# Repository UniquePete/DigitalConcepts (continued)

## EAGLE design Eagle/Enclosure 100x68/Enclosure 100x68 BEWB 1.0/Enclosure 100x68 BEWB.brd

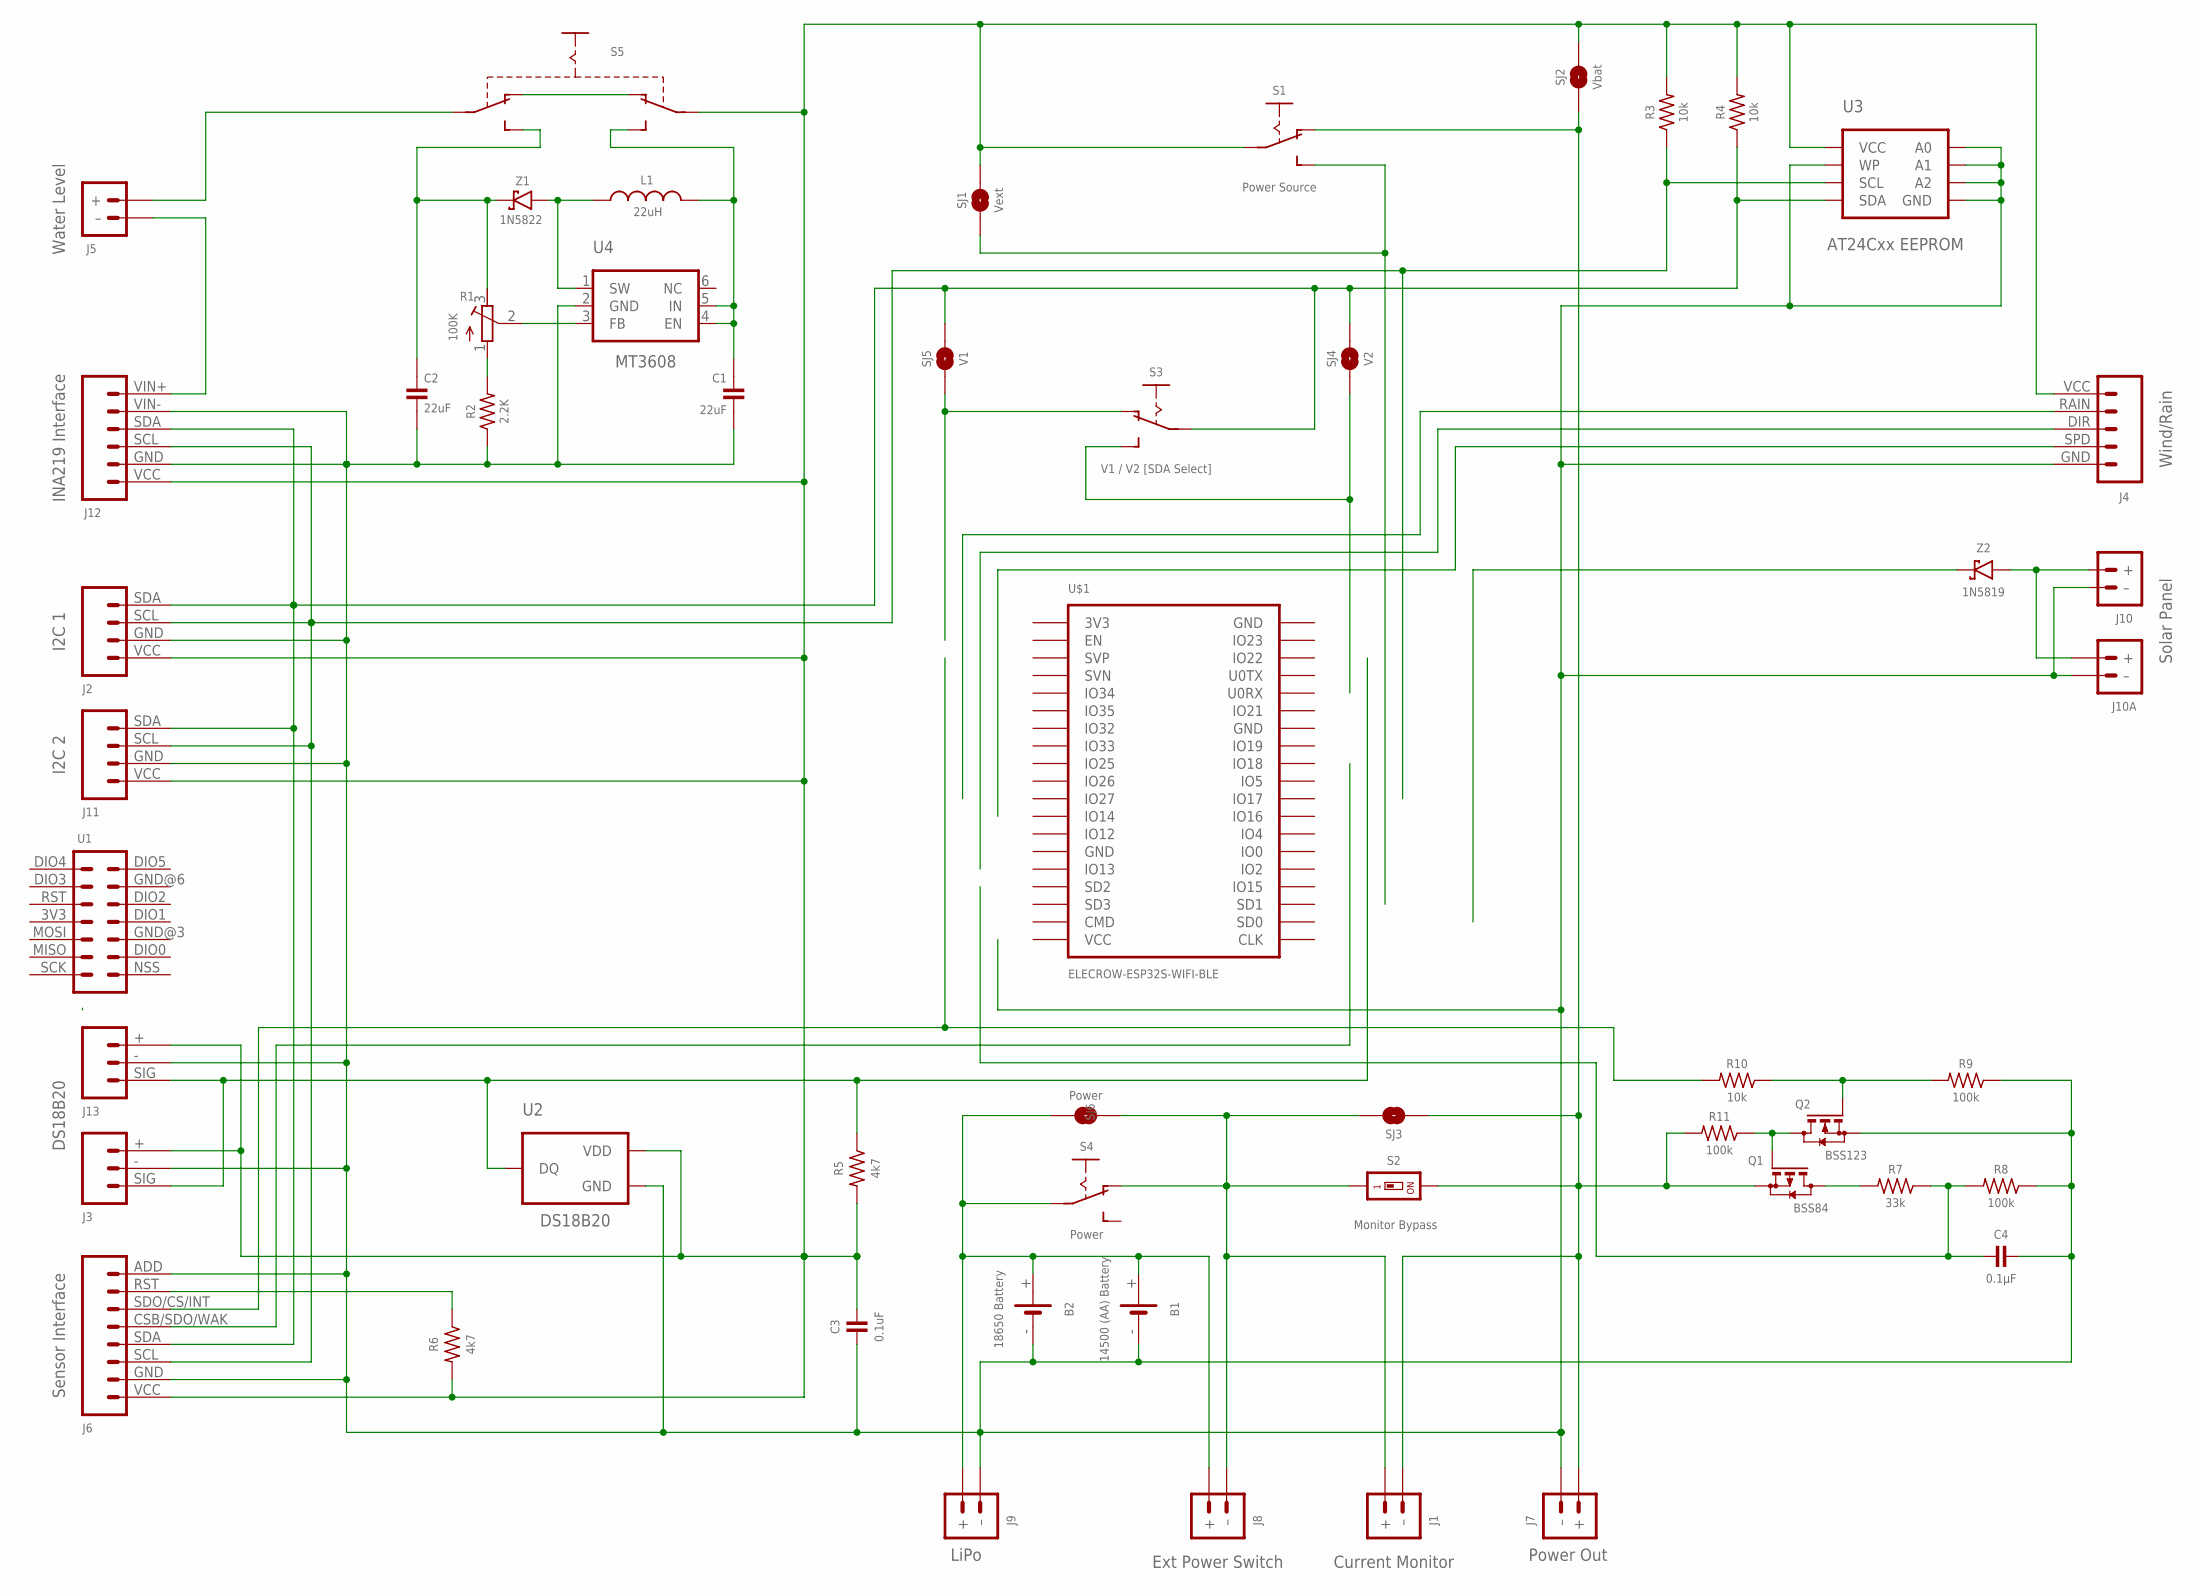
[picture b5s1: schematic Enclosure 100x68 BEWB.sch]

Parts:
B1: 14500 (AA) Battery; BATTERY-14500
B2: 18650 Battery; BATTERY-18650
C1, C2: 22uF; C1206
C3: 0.1uF; C0805
C4: 0.1µF; C0805
J1: Current Monitor; JST-PH2.0-2-HORIZONTAL
J2: I2C 1; JST-PH2.0-4-VERTICAL-I2C
J3: DS18B20; JST-PH2.0-3-VERTICAL-SIG
J4: Wind/Rain; JST-PH2.0-5-DUAL-WEATHER
J5: Water Level; JST-PH2.0-2-DUAL-POWER
J6: Sensor Interface; CONN_08-SENSOR
J7: Power Out; JST-GH1.25-2-HORIZONTAL
J8: Ext Power Switch; JST-PH2.0-2-DUAL-POWER
J9: LiPo; JST-PH2.0-2-HORIZONTAL-POWER
J10: Solar Panel; JST-PH2.0-2-VERTICAL=POWER
J10A: JST-PH2.0-2-HORIZONTAL-POWERJST-PTH-2; JST-PH2.0-2-HORIZONTAL-POWER
J11: I2C 2; JST-PH2.0-4-HORIZONTAL
J12: INA219 Interface; CONN_06-INA219
J13: JST-PH2.0-3-HORIZONTAL-DS18B20; JST-PH2.0-DS18B20-HORIZONTAL
L1: 22uH; CDRH104R+
Q1: BSS84; SOT23-3
Q2: BSS123; SOT23-3
R1: 100K; RTRIM64P
R2: 2.2K; R0805
R3, R4, R10: 10k; R0805
R5, R6: 4k7; R0805
R7: 33k; R0805
R8, R9, R11: 100k; R0805
S1: Power Source; SWITCH-SPDT-SMT
S2: Monitor Bypass; SMD-001
S3: V1 / V2 [SDA Select]; SWITCH-SPDT-SMT
S4: Power; SWITCH-SPDT-PTH
S5: SWITCH-SLIDE-DPDT-PTH-S; SWITCH-DPDT-PTH
SJ1: Vext; SJ
SJ2: Vbat; SJ-VIA-2
SJ3: Monitor; SJ
SJ4: V2; SJ
SJ5: V1; SJ
SJ6: Power; SJ
U1: RFM95W-PI-HEADER; RFM95W-PI
U2: DS18B20; TO-92
U3: AT24Cxx EEPROM; SOP-8
U4: MT3608; SOT-23-6
U$1: ELECROW-ESP32S-WIFI-BLE
Z1: 1N5822; DIODE_SMB
Z2: 1N5819; SOD-123

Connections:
GND: B1.-, B2.-, C1.2, C2.2, C3.2, C4.2, J2.GND (3), J3.- (2), J4.GND (5), J6.ADD (8), J6.GND (2), J7.- (–), J9.- (–), J10.- (–), J10A.- (–), J11.GND (2), J12.GND (2), J12.VIN- (5), J13.- (2), Q2.2 (S), R2.1, R8.1, R9.1, U2.1 (GND), U3.P$1 (A0), U3.P$2 (A1), U3.P$3 (A2), U3.P$4 (GND), U3.P$7 (WP), U4.2 (GND)
unnamed: J10.+, J10A.+, Z2.A
unnamed: B1.+, B2.+, J8.+, J9.+, S4.2, SJ6.2
unnamed: L1.1, U4.1 (SW), Z1.A
unnamed: Q1.3 (D), R7.2
unnamed: J2.SCL (2), J6.SCL (3), J11.SCL (3), J12.SCL (3), R3.1, U3.P$6 (SCL)
unnamed: J6.RST (7), R6.1
unnamed: J2.SDA (1), J6.SDA (4), J11.SDA (4), J12.SDA (4), R4.1, S3.2, SJ4.2, SJ5.2, U3.P$5 (SDA)
unnamed: S1.3 (S), SJ1.1
unnamed: J5.- (–), J12.VIN+ (6)
unnamed: C4.1, R7.1, R8.2
unnamed: J5.+, S5.P$2 (P1)
unnamed: J1.1 (+), J8.- (–), S2.1, S4.1 (O), SJ3.2, SJ6.1
unnamed: R1.2 (S), U4.3 (FB)
unnamed: R1.1 (A), R2.2
unnamed: J3.SIG (1), J13.SIG (1), R5.1, U2.2 (DQ)
unnamed: C1.1, L1.2, S5.P$6 (S2), U4.4 (EN), U4.5 (IN)
unnamed: S5.P$1 (O1), S5.P$4 (O2)
unnamed: S3.1 (O), SJ5.1
unnamed: C2.1, R1.3 (E), S5.P$3 (S1), Z1.C
unnamed: S3.3 (S), SJ4.1
unnamed: J6.SDO/CS/INT (6), R10.2
unnamed: J1.2 (–), J7.+, Q1.2 (S), R11.2, S1.1 (O), S2.2, SJ2.1, SJ3.1
unnamed: Q1.1 (G), Q2.3 (D), R11.1
unnamed: Q2.1 (G), R9.2, R10.1
VEXT: C3.1, J2.VCC (4), J3.+ (3), J4.VCC (1), J6.VCC (1), J11.VCC (1), J12.VCC (1), J13.+ (3), R3.2, R4.2, R5.2, R6.2, S1.2, S5.P$5 (P2), SJ1.2, SJ2.2, SJ2.2@V (2), U2.3 (VDD), U3.P$8 (VCC)

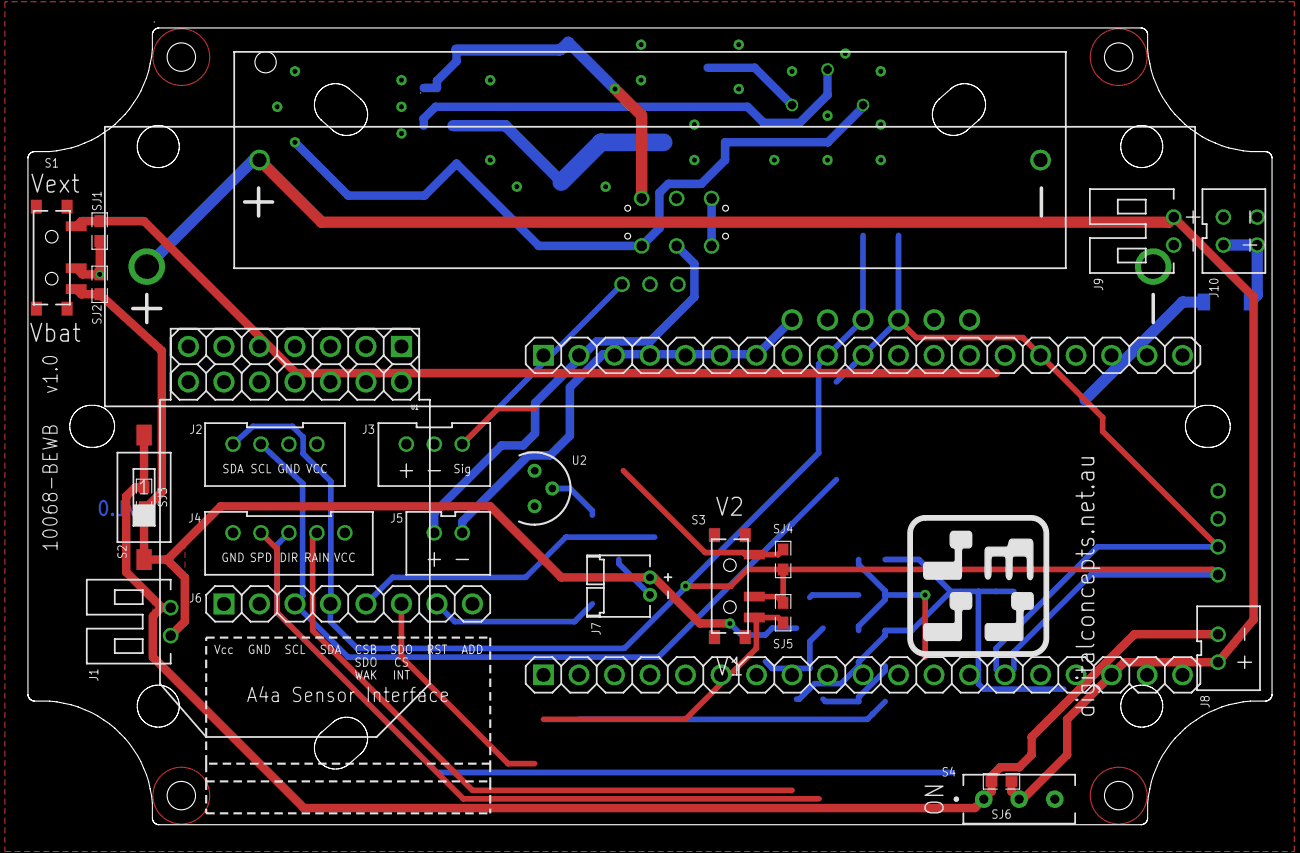
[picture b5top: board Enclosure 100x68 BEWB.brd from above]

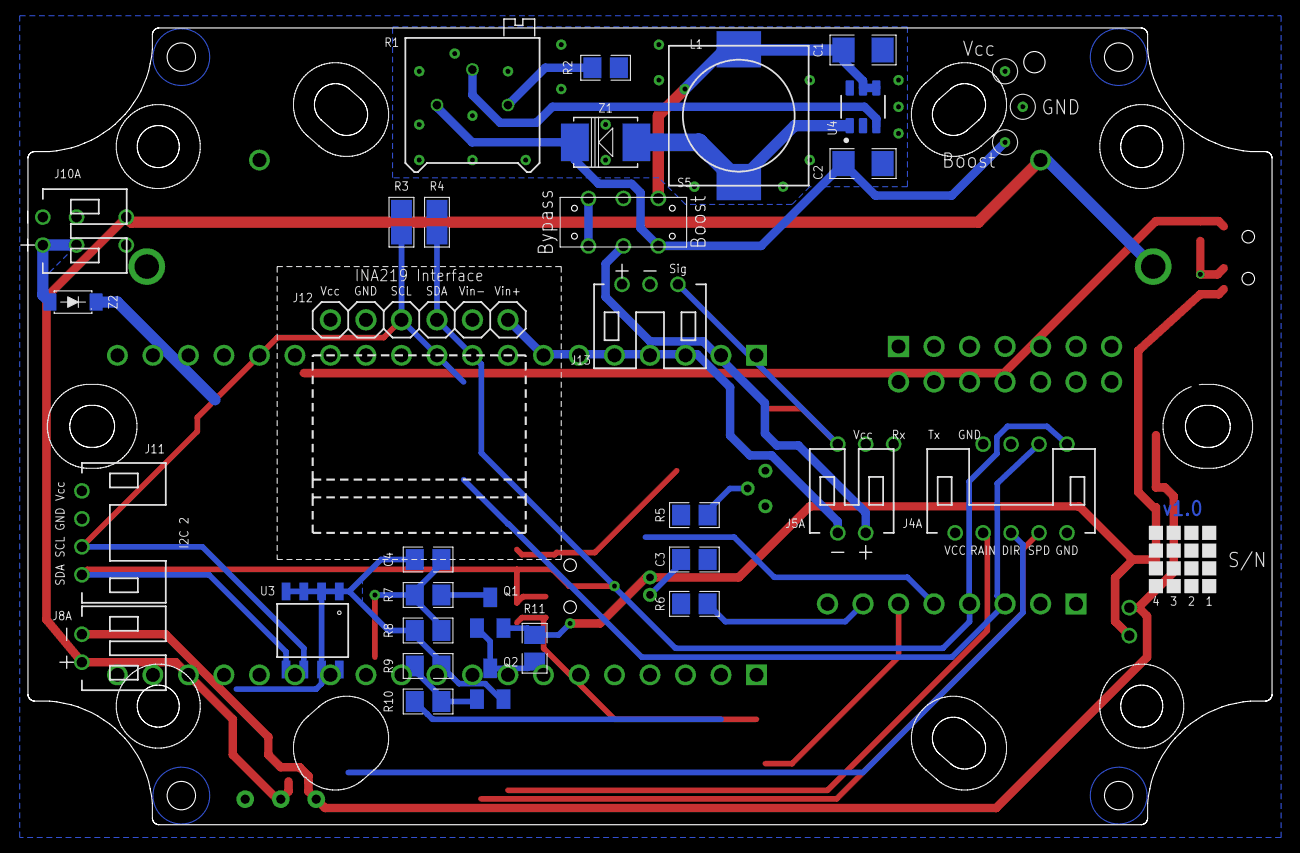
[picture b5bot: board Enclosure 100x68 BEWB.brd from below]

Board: 2 copper layers, 89.0 x 57.0 mm, 52 parts (30 on the bottom side), 26 nets.

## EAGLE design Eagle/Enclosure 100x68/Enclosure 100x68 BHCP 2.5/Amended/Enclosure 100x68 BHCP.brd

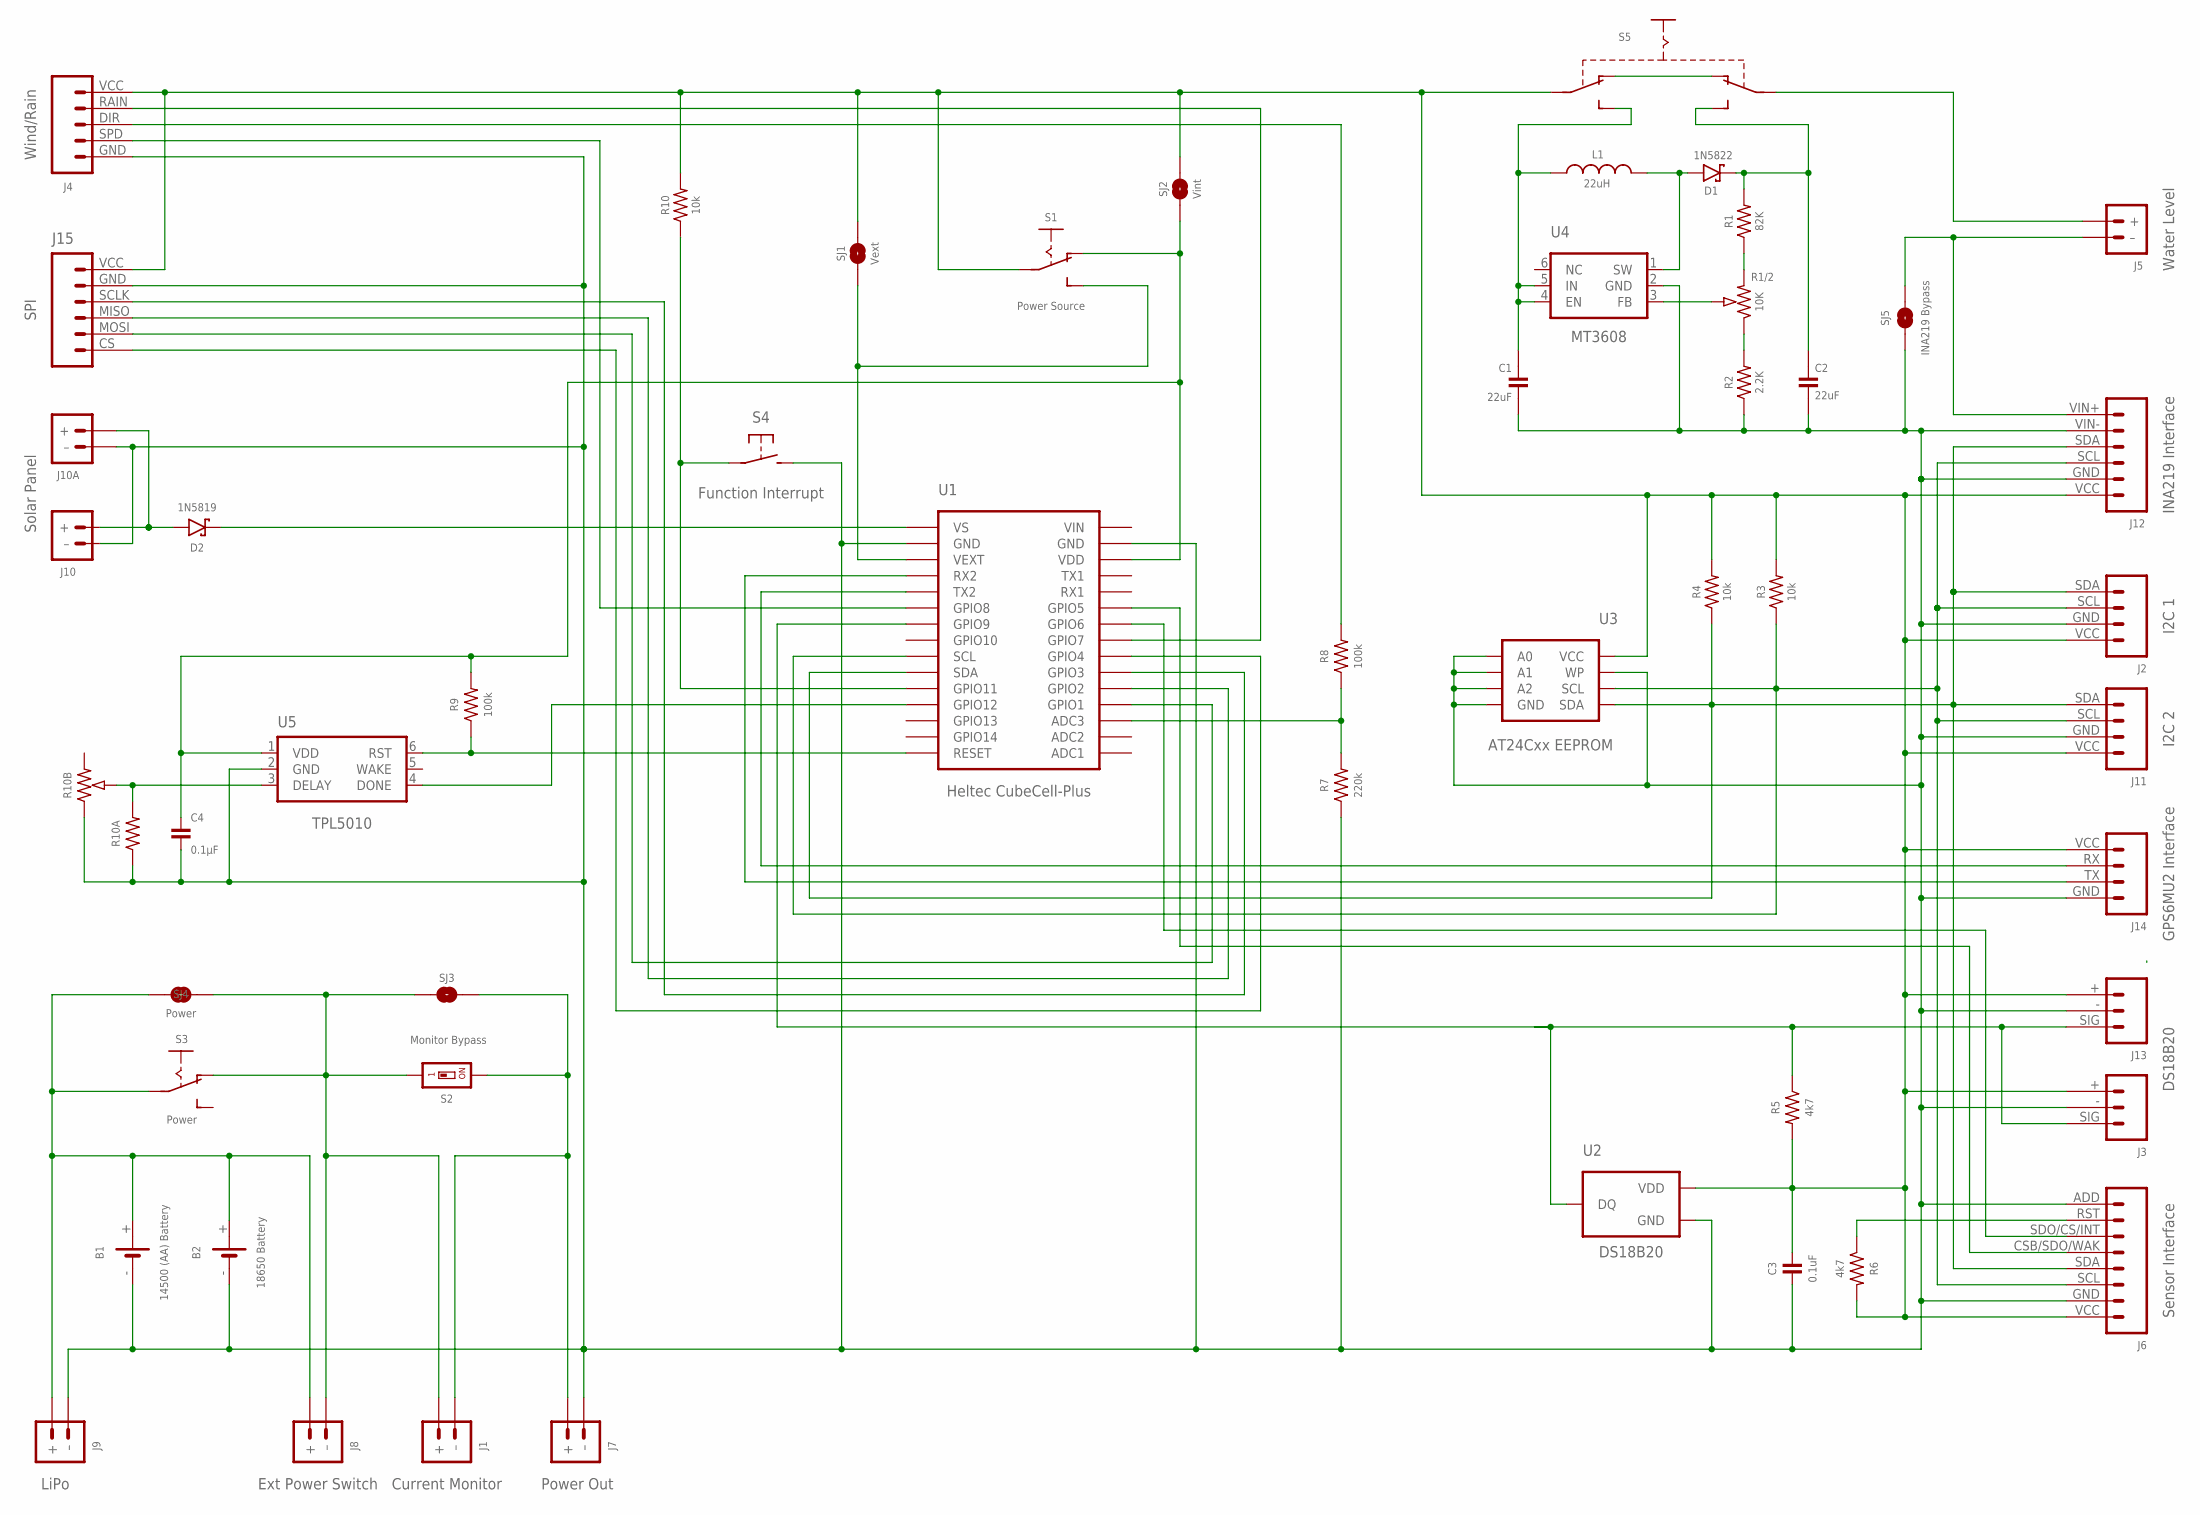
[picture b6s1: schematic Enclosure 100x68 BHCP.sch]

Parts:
B1: 14500 (AA) Battery; BATTERY-14500
B2: 18650 Battery; BATTERY-18650
C1, C2: 22uF; C1206
C3: 0.1uF; C0805
C4: 0.1µF; C0805
D1: 1N5822; DIODE_SMB
D2: 1N5819; SOD-123
J1: Current Monitor; JST-PH2.0-2-HORIZONTAL
J2: I2C 1; JST-PH2.0-4-VERTICAL-I2C
J3: DS18B20; JST-PH2.0-3-VERTICAL-SIG
J4: Wind/Rain; JST-PH2.0-5-DUAL-WEATHER
J5: Water Level; JST-PH2.0-2-DUAL-POWER
J6: Sensor Interface; CONN_08-SENSOR
J7: Power Out; JST-GH1.25-2-HORIZONTAL
J8: Ext Power Switch; JST-PH2.0-2-DUAL-POWER
J9: LiPo; JST-PH2.0-2-HORIZONTAL-POWER
J10: Solar Panel; JST-PH2.0-2-VERTICAL=POWER
J10A: JST-PH2.0-2-HORIZONTAL-POWERJST-PTH-2; JST-PH2.0-2-HORIZONTAL-POWER
J11: I2C 2; JST-PH2.0-4-HORIZONTAL
J12: INA219 Interface; CONN_06-INA219
J13: JST-PH2.0-3-HORIZONTAL-DS18B20; JST-PH2.0-DS18B20-HORIZONTAL
J14: GPS6MU2 Interface; CONN_04-GPS
J15: SPI; JST-PH2.0-6-HORIZONTAL-SPI
L1: 22uH; CDRH104R+6D28
R1: 82K; R0805
R1/2: 10K; RTRIM64P
R2: 2.2K; R0805
R3, R4, R10: 10k; R0805
R5, R6: 4k7; R0805
R7: 220k; R0805
R8, R9: 100k; R0805
R10A: RESISTORR0805; R0805
R10B: RESISTOR-TRIMM-33-US; RTRIM3*3
S1: Power Source; SWITCH-SPDT-SMT
S2: Monitor Bypass; SMD-001
S3: Power; SWITCH-SPDT-PTH
S4: Function Interrupt; SWITCH-2-PAD
S5: SWITCH-SLIDE-DPDT-PTH-S; SWITCH-DPDT-PTH
SJ1: Vext; SJ
SJ2: Vint; SJ-VIA-12
SJ3: Monitor; SJ
SJ4: Power; SJ
SJ5: INA219 Bypass; SJ
U1: Heltec CubeCell-Plus; HELTEC-CUBECELL=PLUS-X
U2: DS18B20; TO-92
U3: AT24Cxx EEPROM; SOP-8
U4: MT3608; SOT-23-6
U5: TPL5010; SOT-23-6

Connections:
GND: B1.-, B2.-, C1.2, C2.2, C3.2, C4.2, J2.GND (3), J3.- (2), J4.GND (5), J6.ADD (8), J6.GND (2), J7.- (–), J9.- (–), J10.- (–), J10A.- (–), J11.GND (2), J12.GND (2), J12.VIN- (5), J13.- (2), J14.GND (4), J15.GND (5), R2.1, R7.1, R10A.1, R10B.1 (A), S4.P$2 (S), SJ5.1, U1.GND@14 (GND), U1.GND@17 (GND), U2.1 (GND), U3.P$1 (A0), U3.P$2 (A1), U3.P$3 (A2), U3.P$4 (GND), U3.P$7 (WP), U4.2 (GND), U5.2 (GND)
unnamed: D2.A, J10.+, J10A.+
unnamed: R7.2, R8.1, U1.ADC3
unnamed: J1.2 (–), J7.+, S2.2, SJ3.1
unnamed: B1.+, B2.+, J8.+, J9.+, S3.2, SJ4.2
unnamed: D2.C, U1.VS
unnamed: D1.A, L1.1, U4.1 (SW)
unnamed: J4.DIR (3), R8.2
unnamed: J2.SCL (2), J6.SCL (3), J11.SCL (3), J12.SCL (3), R3.1, U1.SCL, U3.P$6 (SCL)
unnamed: J6.RST (7), R6.1
unnamed: J6.CSB/SDO/WAK (5), U1.GPIO5
unnamed: J2.SDA (1), J6.SDA (4), J11.SDA (4), J12.SDA (4), R4.1, U1.SDA, U3.P$5 (SDA)
unnamed: J4.SPD (4), U1.GPIO8
unnamed: S1.3 (S), SJ1.1, U1.VEXT
unnamed: J14.RX (2), U1.TX2
unnamed: J5.- (–), J12.VIN+ (6), SJ5.2
unnamed: J14.TX (3), U1.RX2
unnamed: R10A.2, R10B.2 (S), U5.3 (DELAY)
unnamed: J6.SDO/CS/INT (6), U1.GPIO6
unnamed: J5.+, S5.P$2 (P1)
unnamed: J1.1 (+), J8.- (–), S2.1, S3.1 (O), SJ3.2, SJ4.1
unnamed: R1/2.2 (S), U4.3 (FB)
unnamed: R1/2.1 (A), R2.2
unnamed: J3.SIG (1), J13.SIG (1), R5.1, U1.GPIO9, U2.2 (DQ)
unnamed: C1.1, L1.2, S5.P$6 (S2), U4.4 (EN), U4.5 (IN)
unnamed: S5.P$1 (O1), S5.P$4 (O2)
unnamed: R10.1, S4.P$1, U1.GPIO11
unnamed: C2.1, D1.C, R1.2, S5.P$3 (S1)
unnamed: J15.MOSI (2), U1.GPIO1
unnamed: J15.MISO (3), U1.GPIO2
unnamed: J4.RAIN (2), U1.GPIO7
unnamed: R9.1, U1.RST (RESET), U5.6 (RST)
unnamed: J15.SCLK (4), U1.GPIO3
unnamed: J15.CS (1), U1.GPIO4
unnamed: U1.GPIO12, U5.4 (DONE)
unnamed: R1.1, R1/2.3 (E)
unnamed: C4.1, R9.2, S1.1 (O), SJ2.1, SJ2.1@V (1), U1.VDD, U5.1 (VDD)
VEXT: C3.1, J2.VCC (4), J3.+ (3), J4.VCC (1), J6.VCC (1), J11.VCC (1), J12.VCC (1), J13.+ (3), J14.VCC (1), J15.VCC (6), R3.2, R4.2, R5.2, R6.2, R10.2, S1.2, S5.P$5 (P2), SJ1.2, SJ2.2, SJ2.2@V (2), U2.3 (VDD), U3.P$8 (VCC)
VIN: U1.VIN

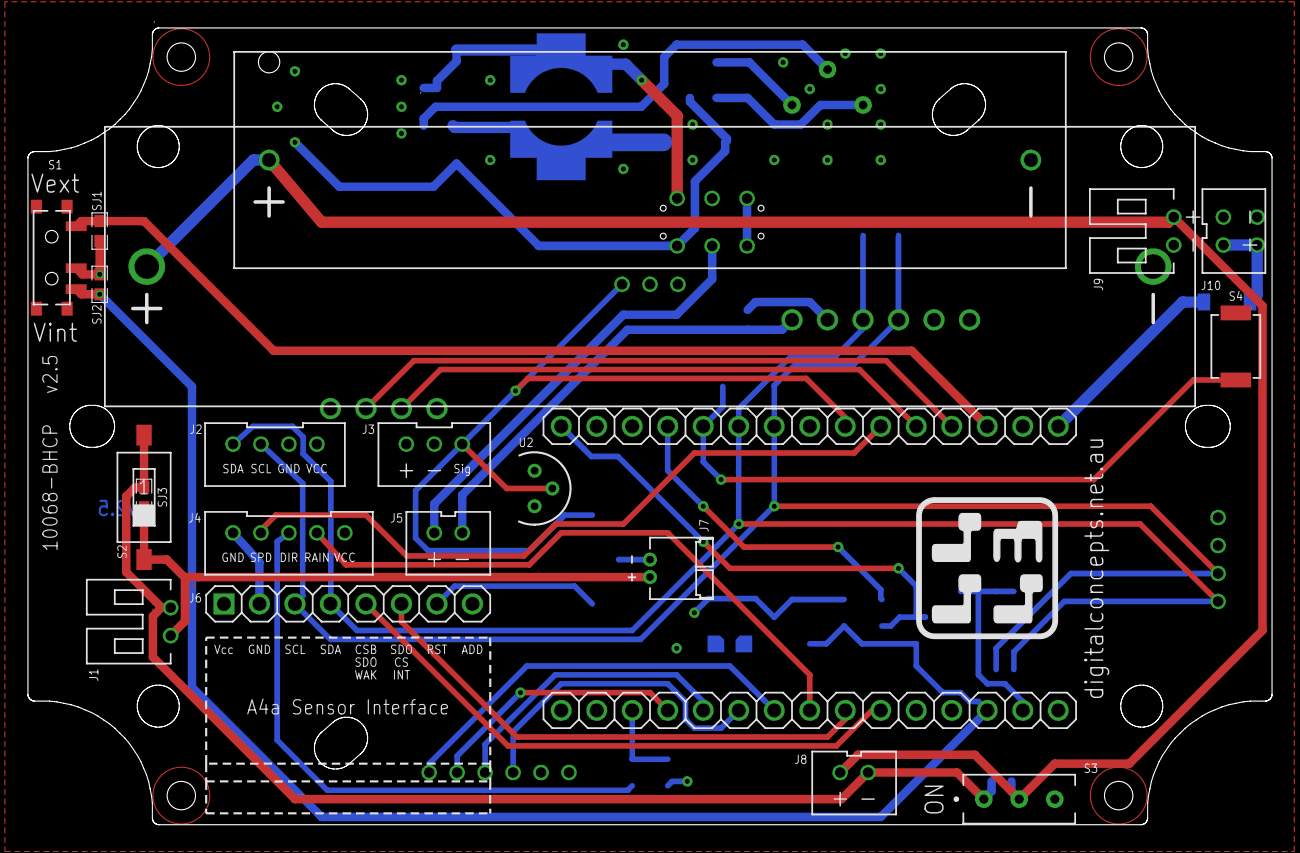
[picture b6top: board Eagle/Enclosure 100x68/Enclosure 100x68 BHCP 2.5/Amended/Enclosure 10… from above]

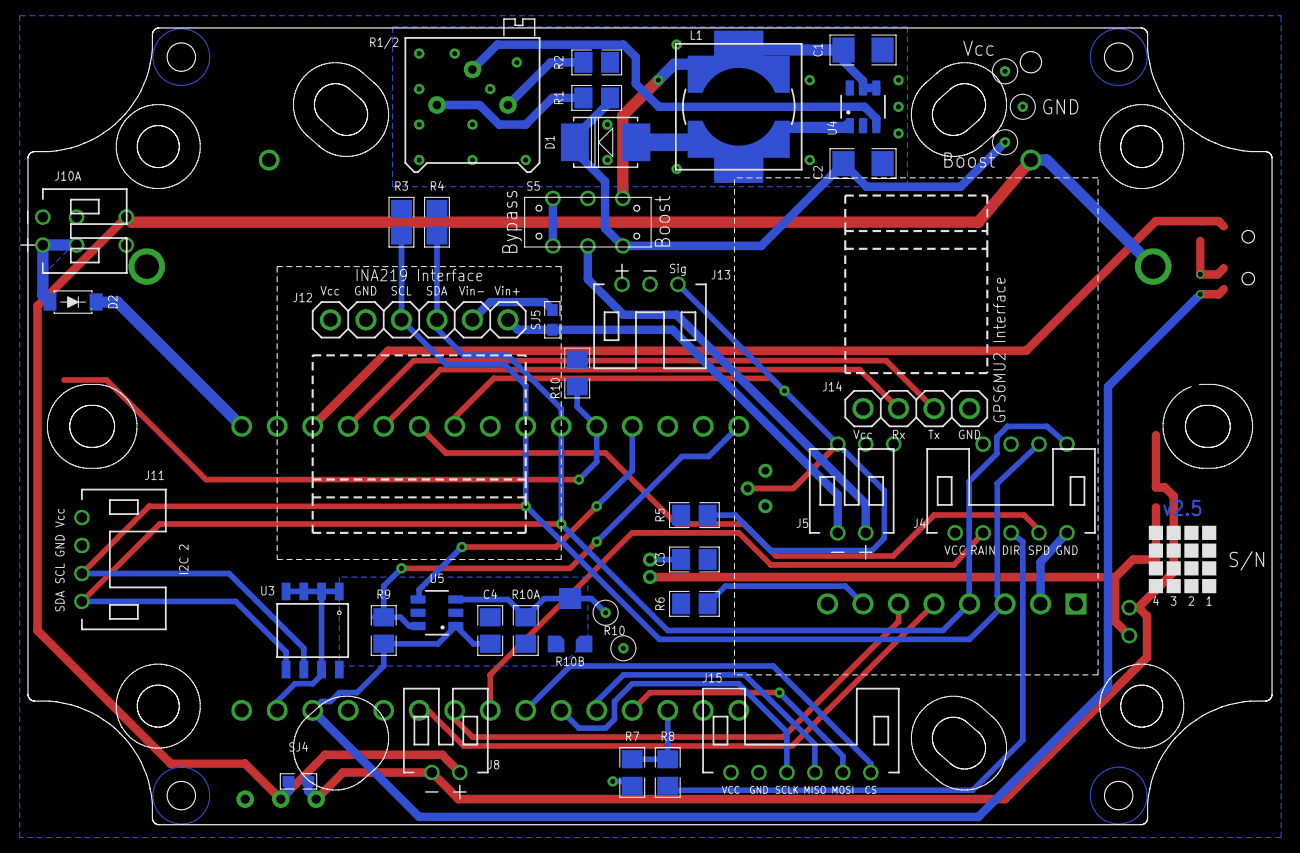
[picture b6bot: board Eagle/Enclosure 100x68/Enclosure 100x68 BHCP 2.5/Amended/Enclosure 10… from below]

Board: 2 copper layers, 89.0 x 57.0 mm, 53 parts (35 on the bottom side), 38 nets.

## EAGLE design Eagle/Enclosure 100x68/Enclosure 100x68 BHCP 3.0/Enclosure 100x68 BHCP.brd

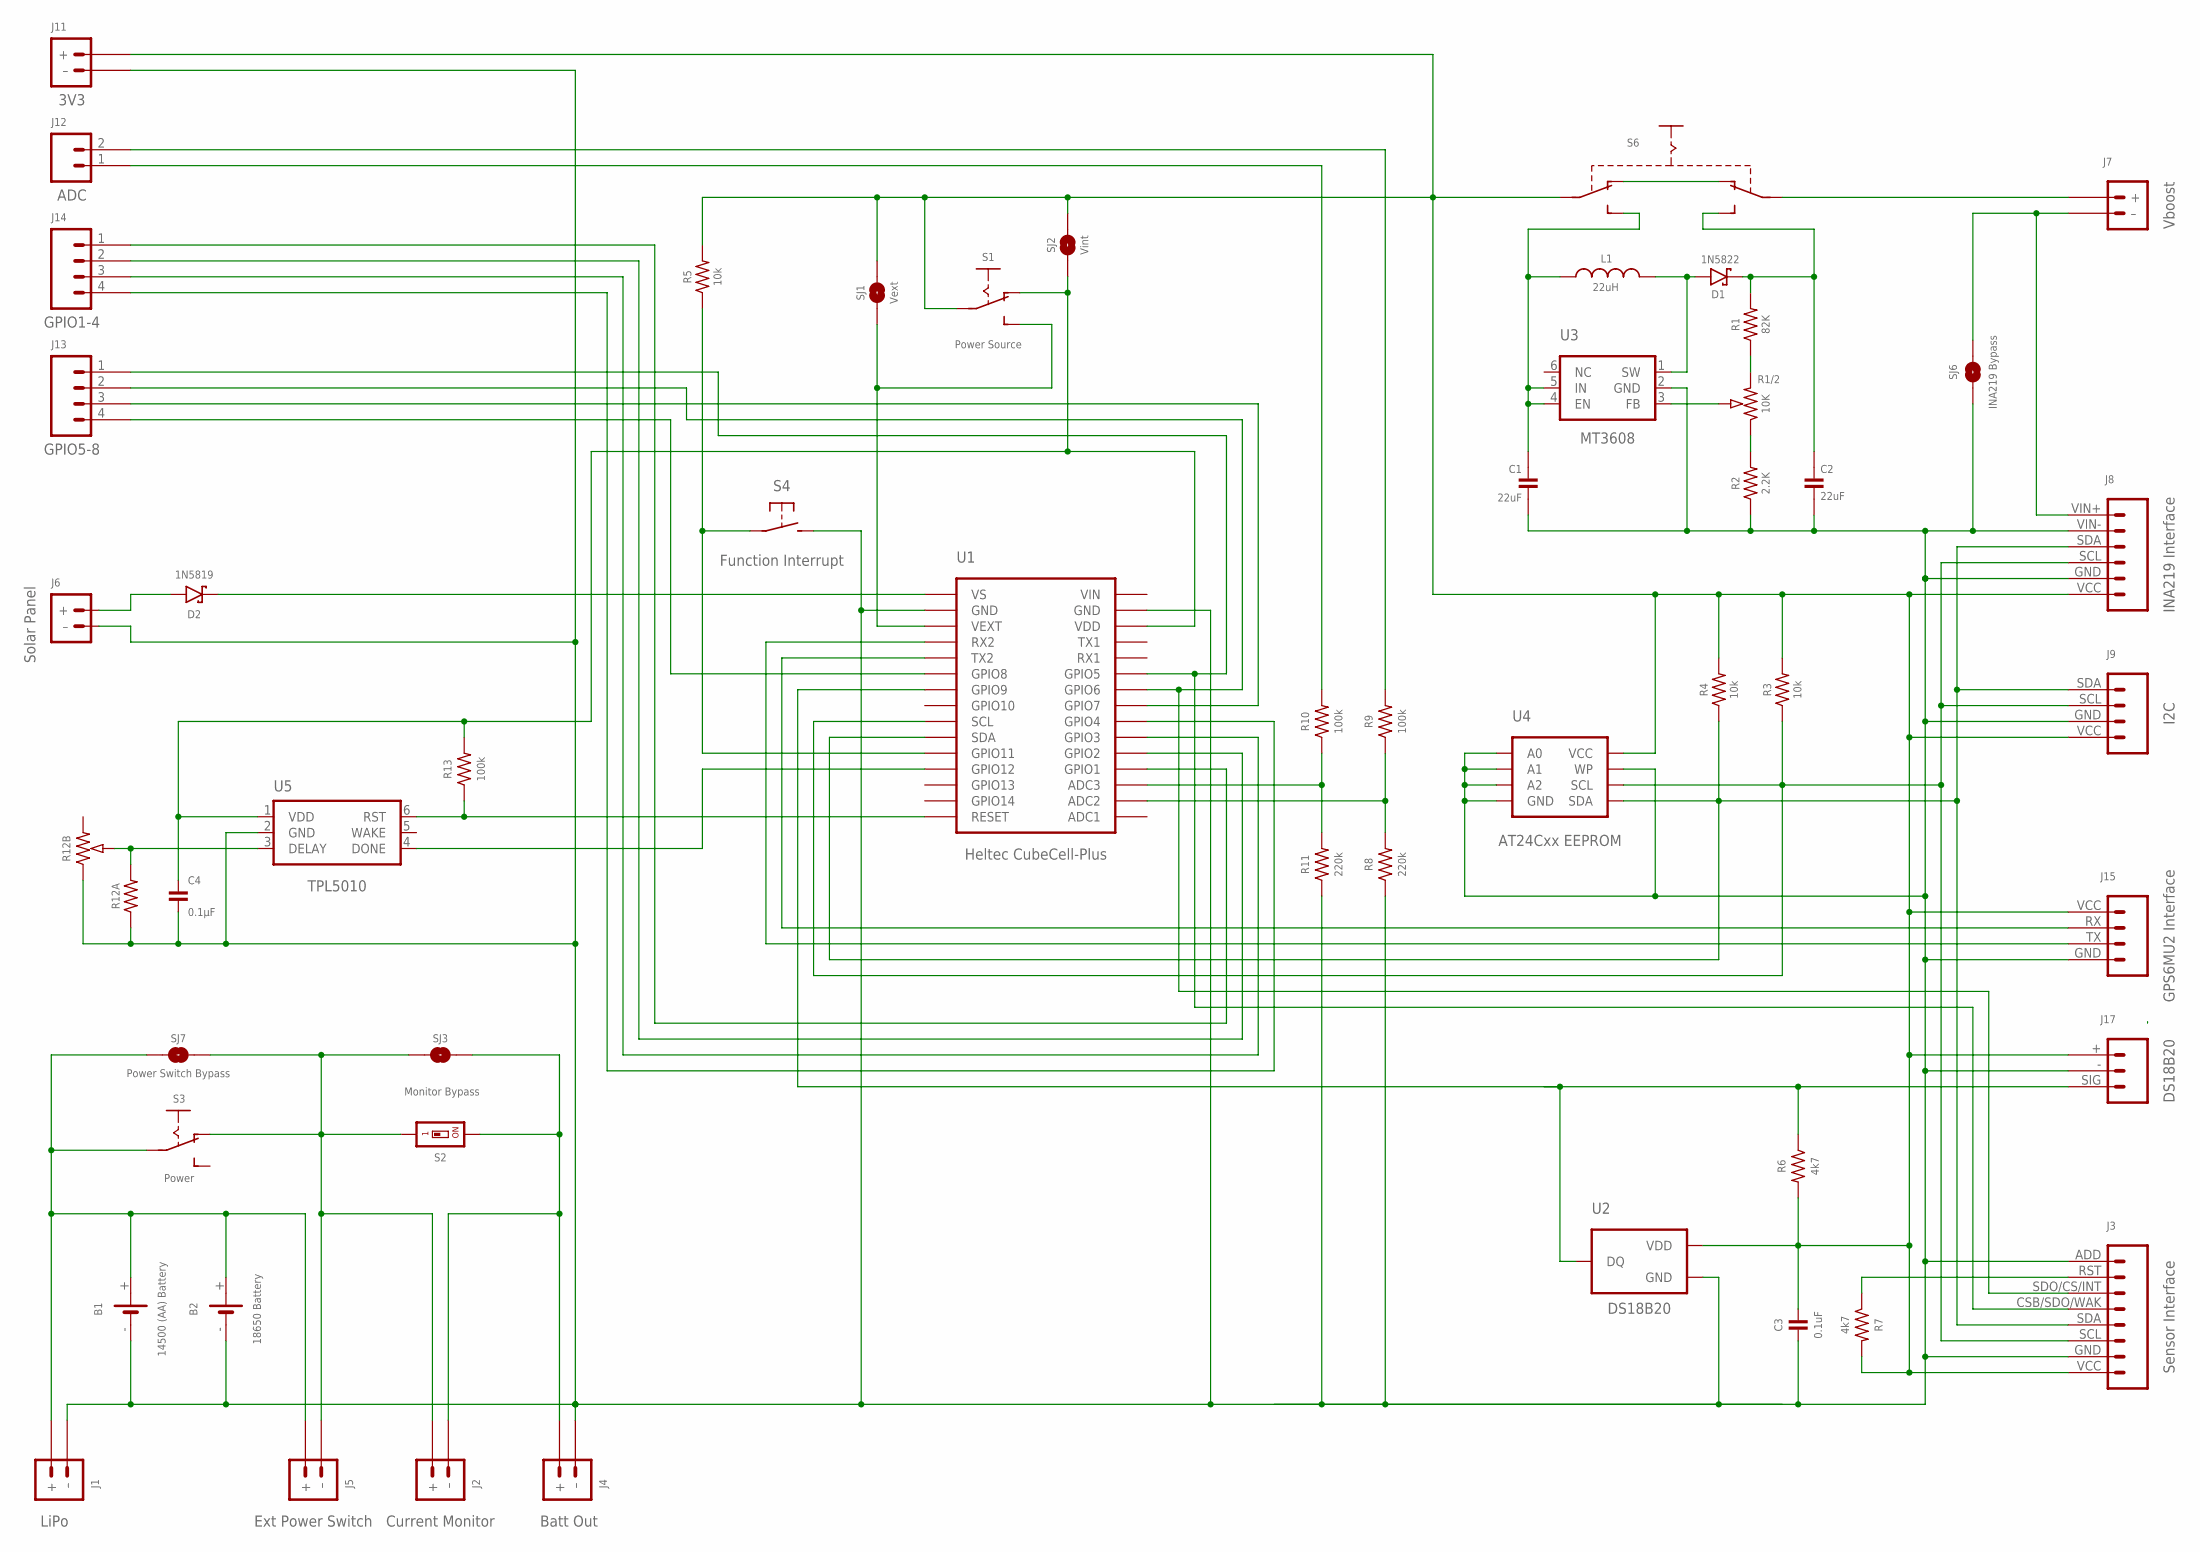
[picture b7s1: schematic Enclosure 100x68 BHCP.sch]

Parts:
B1: 14500 (AA) Battery; BATTERY-14500
B2: 18650 Battery; BATTERY-18650
C1, C2: 22uF; C1206
C3: 0.1uF; C0805
C4: 0.1µF; C0805
D1: 1N5822; DIODE_SMB
D2: 1N5819; SOD-123
J1: LiPo; JST-PH2.0-2-HORIZONTAL-POWER
J2: Current Monitor; JST-PH2.0-2-HORIZONTAL-POWER
J3: Sensor Interface; CONN_08-SENSOR
J4: Batt Out; JST-GH1.25-2-HORIZONTAL
J5: Ext Power Switch; JST-PH2.0-2-DUAL-POWER
J6: Solar Panel; JST-PH2.0-2-VERTICAL=POWER
J7: Vboost; JST-PH2.0-2-HORIZONTAL-POWER
J8: INA219 Interface; CONN_06-INA219
J9: I2C; JST-PH2.0-4-HORIZONTAL@1
J11: 3V3; JST-PH2.0-2-HORIZONTAL-POWER
J12: ADC; JST-PH2.0-2-HORIZONTAL
J13: GPIO5-8; JST-PH2.0-4-HORIZONTAL
J14: GPIO1-4; JST-PH2.0-4-HORIZONTAL
J15: GPS6MU2 Interface; CONN_04-GPS
J17: DS18B20; JST-PH2.0-DS18B20-HORIZONTAL
L1: 22uH; CDRH104R+6D28
R1: 82K; R0805
R1/2: 10K; RTRIM64P
R2: 2.2K; R0805
R3, R4, R5: 10k; R0805
R6, R7: 4k7; R0805
R8, R11: 220k; R0805
R9, R10, R13: 100k; R0805
R12A: RESISTORR0805; R0805
R12B: RESISTOR-TRIMM-33-US; RTRIM3*3
S1: Power Source; SWITCH-SPDT-SMT
S2: Monitor Bypass; SMD-001
S3: Power; SWITCH-SPDT-PTH
S4: Function Interrupt; SWITCH-2-PAD
S6: SWITCH-SLIDE-DPDT-PTH-S; SWITCH-DPDT-PTH
SJ1: Vext; SJ
SJ2: Vint; SJ-VIA-12
SJ3: Monitor; SJ
SJ6: INA219 Bypass; SJ
SJ7: Power Switch Bypass; SJ
U1: Heltec CubeCell-Plus; HELTEC-CUBECELL=PLUS-X
U2: DS18B20; TO-92
U3: MT3608; SOT-23-6
U4: AT24Cxx EEPROM; SOP-8
U5: TPL5010; SOT-23-6

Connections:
GND: B1.-, B2.-, C1.2, C2.2, C3.2, C4.2, J1.- (–), J3.ADD (8), J3.GND (2), J4.- (–), J6.- (–), J8.GND (2), J8.VIN- (5), J9.GND (2), J11.- (–), J15.GND (1), J17.- (2), R2.1, R8.1, R11.1, R12A.1, R12B.1 (A), S4.P$2 (S), SJ6.1, U1.GND@14 (GND), U1.GND@17 (GND), U2.1 (GND), U3.2 (GND), U4.P$1 (A0), U4.P$2 (A1), U4.P$3 (A2), U4.P$4 (GND), U4.P$7 (WP), U5.2 (GND)
unnamed: D2.A, J6.+
unnamed: R10.1, R11.2, U1.ADC3
unnamed: J2.- (–), J4.+, S2.2, SJ3.1
unnamed: B1.+, B2.+, J1.+, J5.+, S3.2, SJ7.2
unnamed: D2.C, U1.VS
unnamed: D1.A, L1.1, U3.1 (SW)
unnamed: J12.1, R10.2
unnamed: J3.SCL (3), J8.SCL (3), J9.SCL (3), R3.1, U1.SCL, U4.P$6 (SCL)
unnamed: J3.RST (7), R7.1
unnamed: J3.CSB/SDO/WAK (5), J13.1 (4), U1.GPIO5
unnamed: J3.SDA (4), J8.SDA (4), J9.SDA (4), R4.1, U1.SDA, U4.P$5 (SDA)
unnamed: J13.4 (1), U1.GPIO8
unnamed: S1.3 (S), SJ1.1, U1.VEXT
unnamed: J15.RX (3), U1.TX2
unnamed: J7.- (–), J8.VIN+ (6), SJ6.2
unnamed: J15.TX (2), U1.RX2
unnamed: R12A.2, R12B.2 (S), U5.3 (DELAY)
unnamed: J3.SDO/CS/INT (6), J13.2 (3), U1.GPIO6
unnamed: J7.+, S6.P$2 (P1)
unnamed: J2.+, J5.- (–), S2.1, S3.1 (O), SJ3.2, SJ7.1
unnamed: R1/2.2 (S), U3.3 (FB)
unnamed: R1/2.1 (A), R2.2
unnamed: J17.SIG (1), R6.1, U1.GPIO9, U2.2 (DQ)
unnamed: C1.1, L1.2, S6.P$6 (S2), U3.4 (EN), U3.5 (IN)
unnamed: S6.P$1 (O1), S6.P$4 (O2)
unnamed: R5.1, S4.P$1, U1.GPIO11
unnamed: C2.1, D1.C, R1.2, S6.P$3 (S1)
unnamed: J14.1 (4), U1.GPIO1
unnamed: J14.2 (3), U1.GPIO2
unnamed: J12.2, R9.2
unnamed: R8.2, R9.1, U1.ADC2
unnamed: R13.1, U1.RST (RESET), U5.6 (RST)
unnamed: J14.3 (2), U1.GPIO3
unnamed: J14.4 (1), U1.GPIO4
unnamed: U1.GPIO12, U5.4 (DONE)
unnamed: R1.1, R1/2.3 (E)
unnamed: C4.1, R13.2, S1.1 (O), SJ2.1, SJ2.1@V (1), U1.VDD, U5.1 (VDD)
unnamed: J13.3 (2), U1.GPIO7
VEXT: C3.1, J3.VCC (1), J8.VCC (1), J9.VCC (1), J11.+, J15.VCC (4), J17.+ (3), R3.2, R4.2, R5.2, R6.2, R7.2, S1.2, S6.P$5 (P2), SJ1.2, SJ2.2, SJ2.2@V (2), U2.3 (VDD), U4.P$8 (VCC)
VIN: U1.VIN
